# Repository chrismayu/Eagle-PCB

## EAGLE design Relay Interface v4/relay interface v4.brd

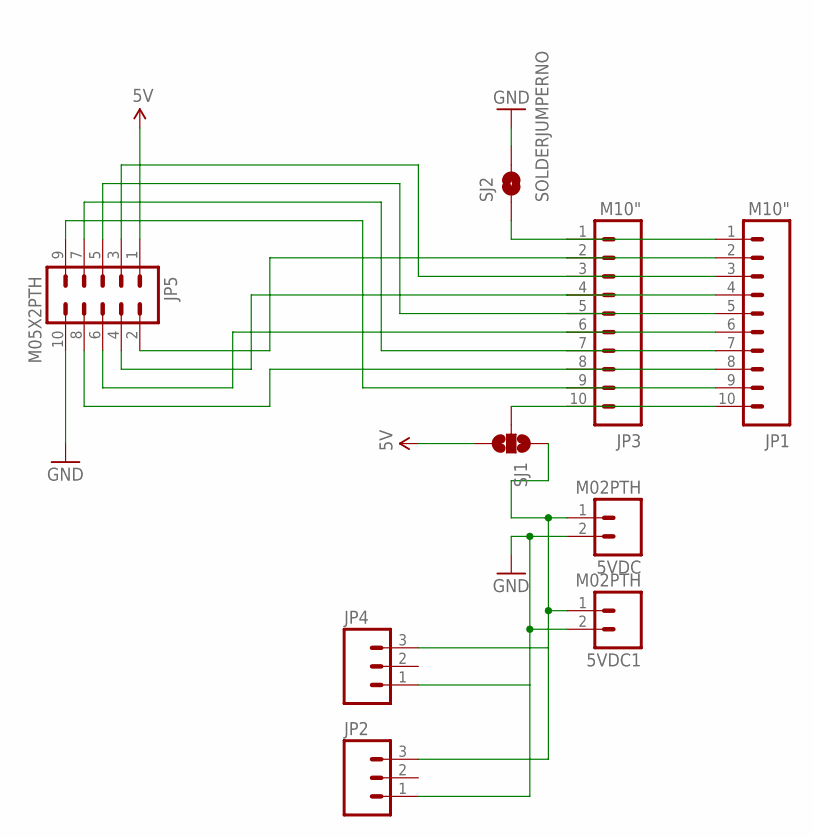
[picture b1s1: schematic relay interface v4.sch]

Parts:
5VDC, 5VDC1: M02PTH; 1X02
JP1, JP3: M10"; 1X10
JP2, JP4: M03PTH; 1X03
JP5: M05X2PTH; AVR_ICSP
SJ1: SOLDERJUMPER_2WAYS; SJ_3
SJ2: SOLDERJUMPERNO; SJ_2S-NO

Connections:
5V: JP5.1, SJ1.3
GND: 5VDC.2, 5VDC1.2, JP2.1, JP4.1, JP5.10, SJ2.2
unnamed: JP1.2, JP3.2, JP5.2
unnamed: JP1.3, JP3.3, JP5.3
unnamed: JP1.4, JP3.4, JP5.4
unnamed: JP1.5, JP3.5, JP5.5
unnamed: JP1.10, JP3.10, SJ1.2
unnamed: JP1.6, JP3.6, JP5.6
unnamed: JP1.7, JP3.7, JP5.7
unnamed: JP1.8, JP3.8, JP5.8
unnamed: JP1.9, JP3.9, JP5.9
unnamed: 5VDC.1, 5VDC1.1, JP2.3, JP4.3, SJ1.1
unnamed: JP1.1, JP3.1, SJ2.1

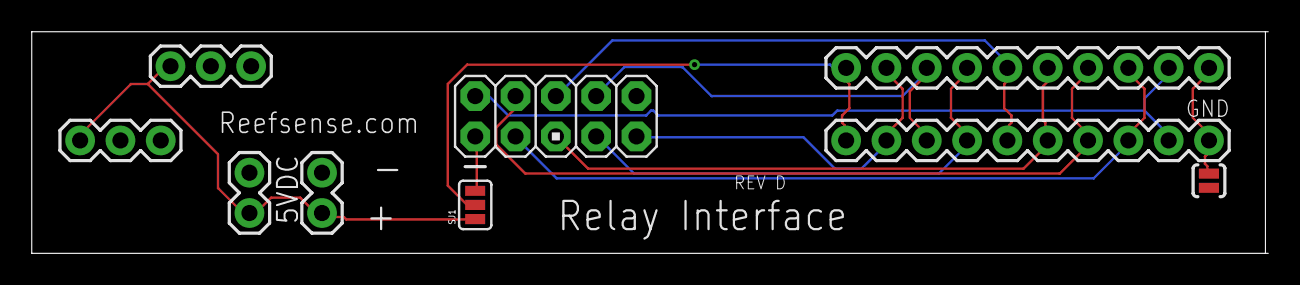
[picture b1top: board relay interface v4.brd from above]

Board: 2 copper layers, 77.7 x 14.0 mm, 9 parts (0 on the bottom side), 13 nets.

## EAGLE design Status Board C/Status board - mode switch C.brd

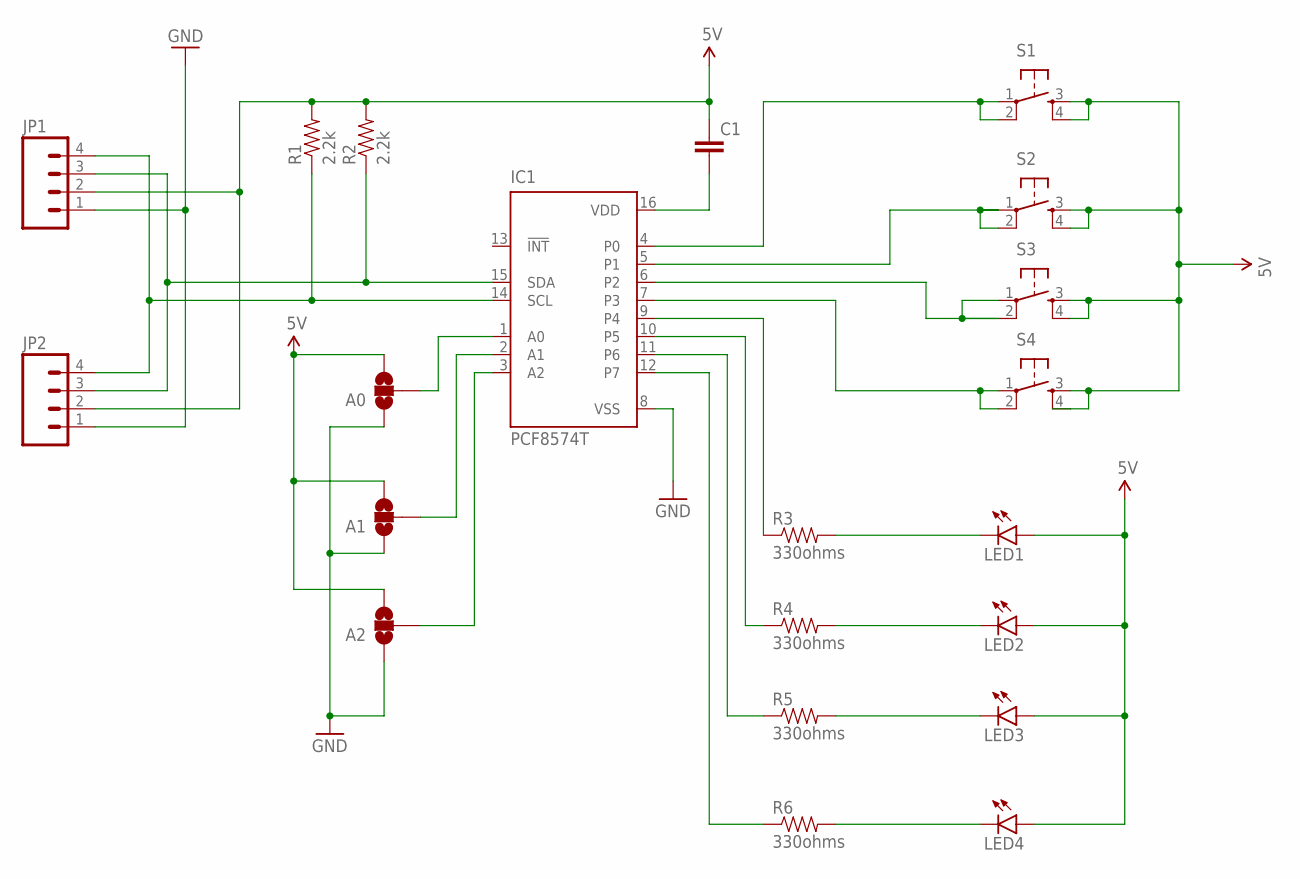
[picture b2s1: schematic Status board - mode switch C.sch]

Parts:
A0, A1, A2: SOLDERJUMPER_2WAYS; SJ_3
C1: CAPPTH2; CAP-PTH-SMALL2
IC1: PCF8574T; SO16W
JP1, JP2: M04PTH; 1X04
LED1, LED2, LED3, LED4: LED3MM
R1, R2: 2.2k; AXIAL-0.3
R3, R4, R5, R6: 330ohms; AXIAL-0.3
S1, S2, S3, S4: TAC_SWITCHPTH; TACTILE-PTH

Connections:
5V: A0.3, A1.3, A2.3, C1.1, JP1.2, JP2.2, LED1.A, LED2.A, LED3.A, LED4.A, R1.P$2 (2), R2.P$2 (2), S1.3, S1.4, S2.3, S2.4, S3.3, S3.4, S4.3, S4.4
GND: A0.1, A1.1, A2.1, IC1.8 (VSS), JP1.1, JP2.1
unnamed: IC1.5 (P1), S2.1, S2.2
unnamed: IC1.7 (P3), S4.1, S4.2
unnamed: IC1.6 (P2), S3.1, S3.2
unnamed: A1.2, IC1.2 (A1)
unnamed: IC1.14 (SCL), JP1.4, JP2.4, R1.P$1 (1)
unnamed: IC1.15 (SDA), JP1.3, JP2.3, R2.P$1 (1)
unnamed: A0.2, IC1.1 (A0)
unnamed: C1.2, IC1.16 (VDD)
unnamed: A2.2, IC1.3 (A2)
unnamed: LED4.K (C), R6.P$2 (2)
unnamed: IC1.9 (P4), R3.P$1 (1)
unnamed: IC1.10 (P5), R4.P$1 (1)
unnamed: IC1.11 (P6), R5.P$1 (1)
unnamed: IC1.12 (P7), R6.P$1 (1)
unnamed: LED3.K (C), R5.P$2 (2)
unnamed: LED2.K (C), R4.P$2 (2)
unnamed: LED1.K (C), R3.P$2 (2)
unnamed: IC1.4 (P0), S1.1, S1.2

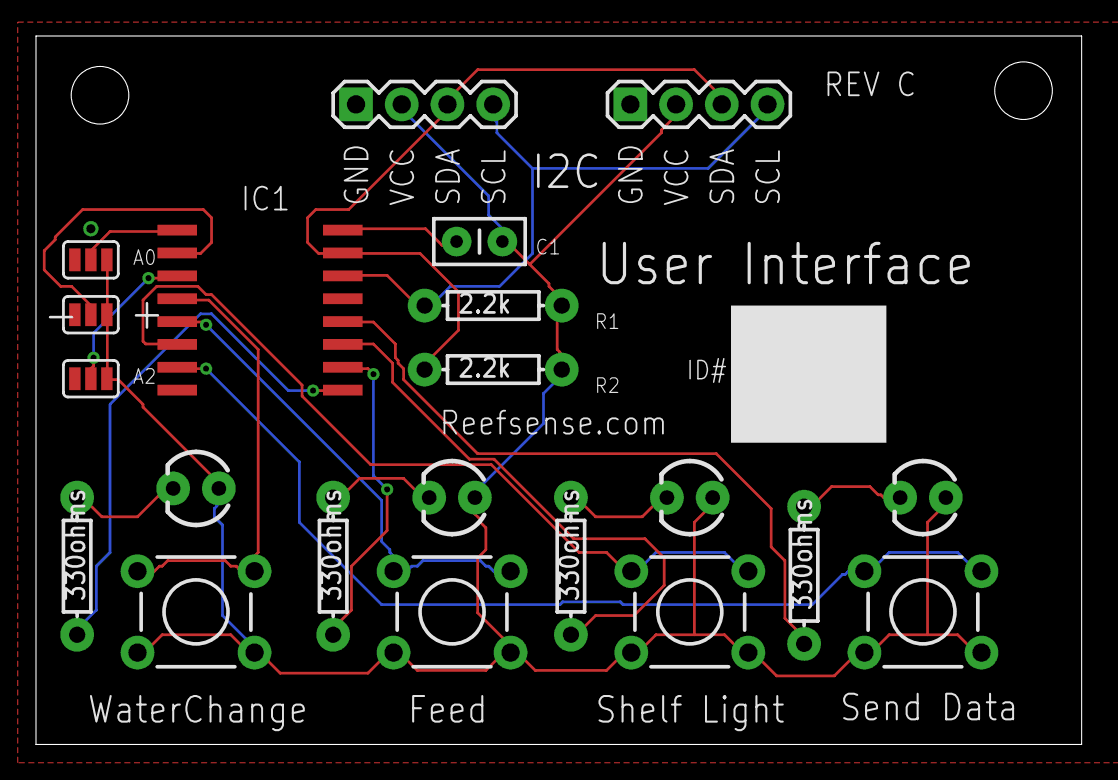
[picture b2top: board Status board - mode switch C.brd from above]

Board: 2 copper layers, 58.1 x 39.4 mm, 21 parts (0 on the bottom side), 20 nets.

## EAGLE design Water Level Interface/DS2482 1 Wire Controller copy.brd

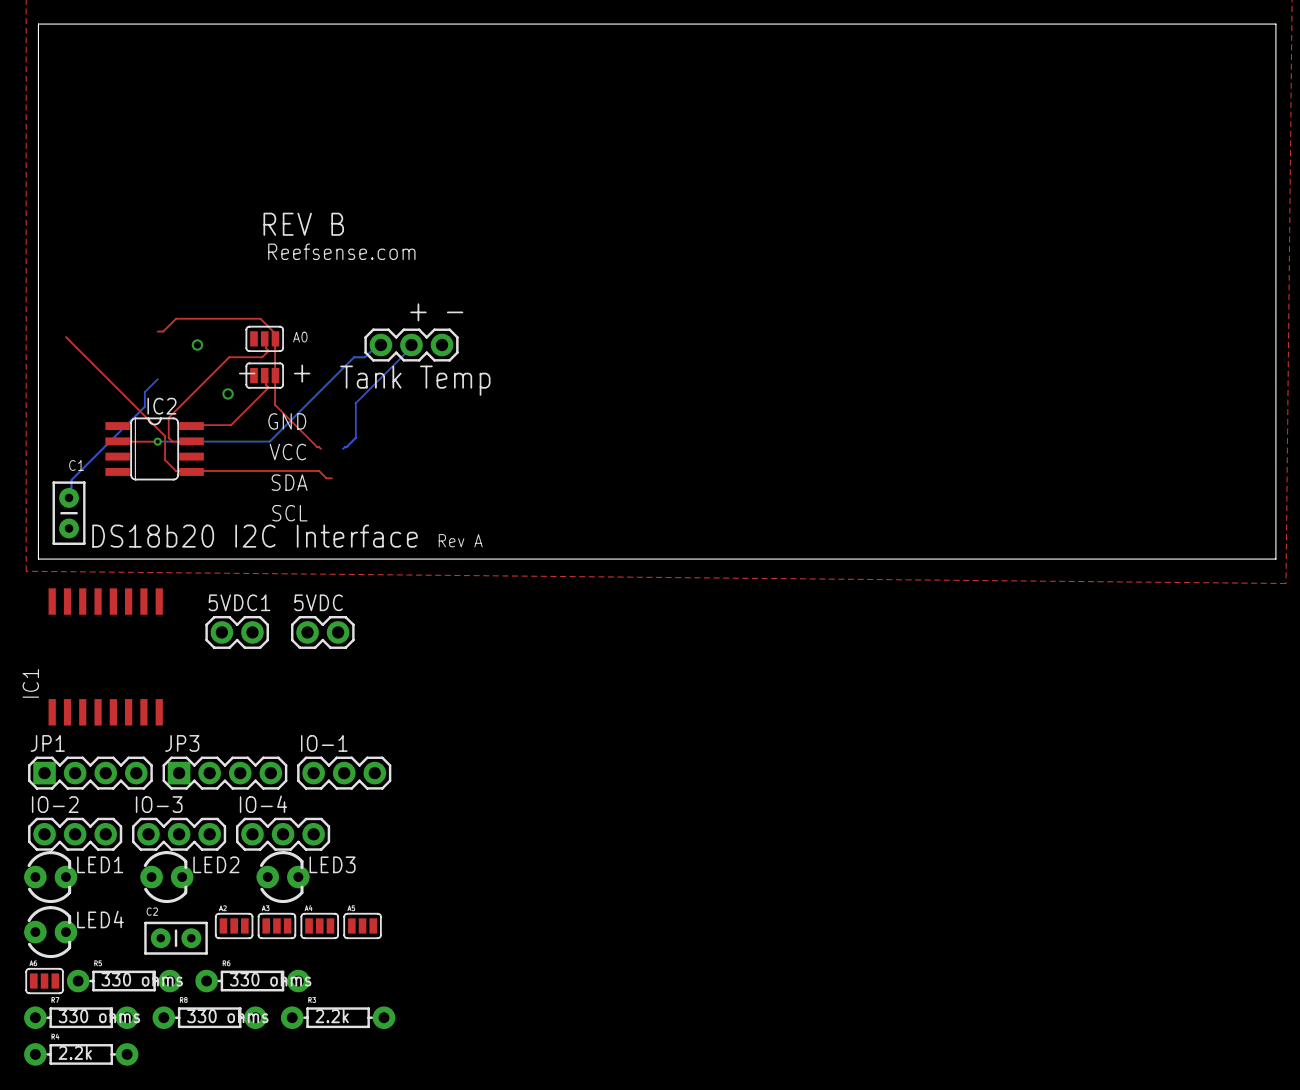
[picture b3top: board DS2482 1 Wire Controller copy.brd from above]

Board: 2 copper layers, 102.8 x 44.4 mm, 30 parts (0 on the bottom side), 27 nets.

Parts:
5VDC, 5VDC1: +; 1X02
A0, A1, A2, A3, A4, A5, A6: SJ_3
C1, C2: CAP-PTH-SMALL2
IC1: PCF8574T; SO16W
IC2: DS2482-100S; SO08
IO-1, IO-2, IO-3, IO-4: 1X03
JP1, JP3: 1X04
JP4: 1X03
LED1, LED2, LED3, LED4: LED3MM
R3, R4: 2.2k; AXIAL-0.3
R5, R6, R7, R8: 330 ohms; AXIAL-0.3

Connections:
5V: A0.3, A1.3, A2.3, A3.3, A4.3, A6.1, C1.1, C2.1, JP1.2, JP3.2, JP4.2, LED1.A, LED2.A, LED3.A, LED4.A, R3.P$2, R4.P$2
GND: A0.1, A1.1, A2.1, A3.1, A4.1, A5.3, C1.2, IC1.8, IC2.3, JP1.1, JP3.1, JP4.3
unnamed: IC1.14, IC2.4, JP1.4, JP3.4, R4.P$1
unnamed: A2.2, IC1.1
unnamed: A0.2, IC2.7
unnamed: IC1.15, IC2.5, JP1.3, JP3.3, R3.P$1
unnamed: A1.2, IC2.8
unnamed: C2.2, IC1.16
unnamed: A3.2, IC1.2
unnamed: A4.2, IC1.3
unnamed: IC1.10, R6.P$1
unnamed: IC2.2, JP4.1
unnamed: IC1.11, R7.P$1
unnamed: IC1.12, R8.P$1
unnamed: IC1.4, IO-1.1
unnamed: IC1.5, IO-2.1
unnamed: IC1.6, IO-3.1
unnamed: IC1.7, IO-4.1
unnamed: IC1.9, R5.P$1
unnamed: LED1.K, R5.P$2
unnamed: LED2.K, R6.P$2
unnamed: LED3.K, R7.P$2
unnamed: LED4.K, R8.P$2
unnamed: A6.2, IO-1.2, IO-2.2, IO-3.2, IO-4.2
unnamed: 5VDC.1, 5VDC1.1, A6.3
unnamed: 5VDC.2, 5VDC1.2, A5.1
unnamed: A5.2, IO-1.3, IO-2.3, IO-3.3, IO-4.3

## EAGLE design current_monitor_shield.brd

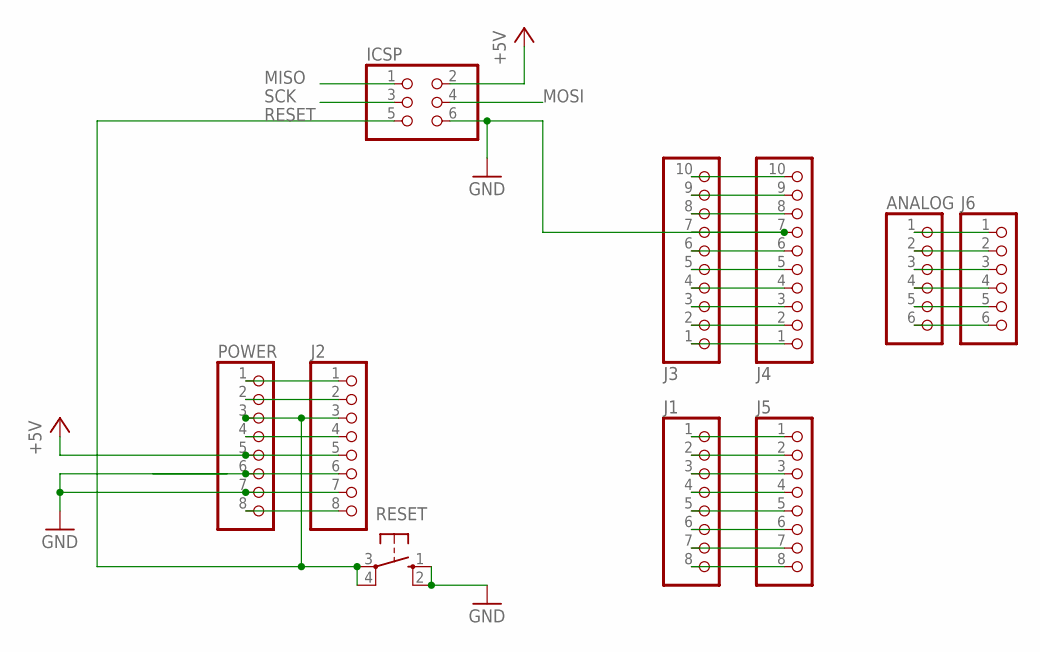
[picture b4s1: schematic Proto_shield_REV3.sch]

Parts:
ANALOG: PINHD-1X6; 1X06
ICSP: PINHD-2X3; 2X03
J1, J2, J5: PINHD-1X8TH; 1X08-TH
J3, J4: PINHD-1X10TH; 1X10-TH
J6: PINHD-1X6; 1X06
POWER: PINHD-1X8TH; 1X08-TH
RESET: 10-XX; B3F-10XX

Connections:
+5V: ICSP.2, J2.5, POWER.5
+9V: J2.8, POWER.8
GND: ICSP.6, J2.7, J3.7, J4.7, POWER.7, RESET.1 (S), RESET.2 (S1)
MISO: ICSP.1
MOSI: ICSP.4
unnamed: J3.6, J4.6
unnamed: J3.1, J4.1
unnamed: J3.4, J4.4
unnamed: J3.5, J4.5
unnamed: J3.2, J4.2
unnamed: J3.3, J4.3
unnamed: J1.1, J5.1
unnamed: J1.2, J5.2
unnamed: J1.3, J5.3
unnamed: J1.4, J5.4
unnamed: J1.5, J5.5
unnamed: J1.6, J5.6
unnamed: J1.7, J5.7
unnamed: J1.8, J5.8
unnamed: ANALOG.1, J6.1
unnamed: ANALOG.2, J6.2
unnamed: ANALOG.3, J6.3
unnamed: ANALOG.4, J6.4
unnamed: ANALOG.5, J6.5
unnamed: ANALOG.6, J6.6
unnamed: J2.6, POWER.6
unnamed: J2.2, POWER.2
unnamed: J2.1, POWER.1
unnamed: J3.9, J4.9
unnamed: J3.10, J4.10
unnamed: J3.8, J4.8
unnamed: J2.4, POWER.4
RESET: ICSP.5, J2.3, POWER.3, RESET.3, RESET.4 (P1)
SCK: ICSP.3

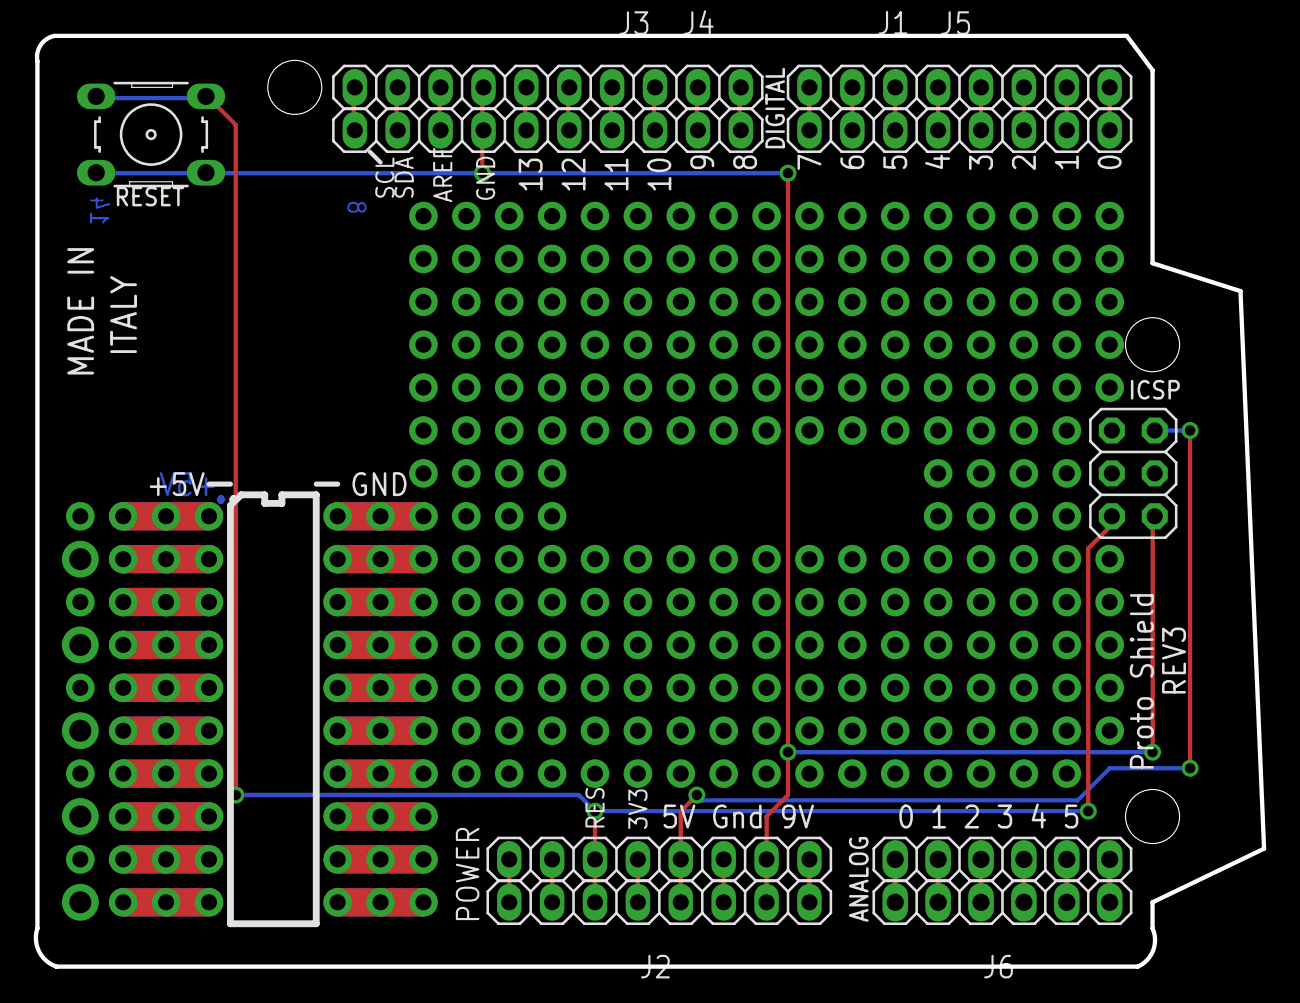
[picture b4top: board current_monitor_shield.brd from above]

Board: 2 copper layers, 72.7 x 55.1 mm, 10 parts (0 on the bottom side), 31 nets.

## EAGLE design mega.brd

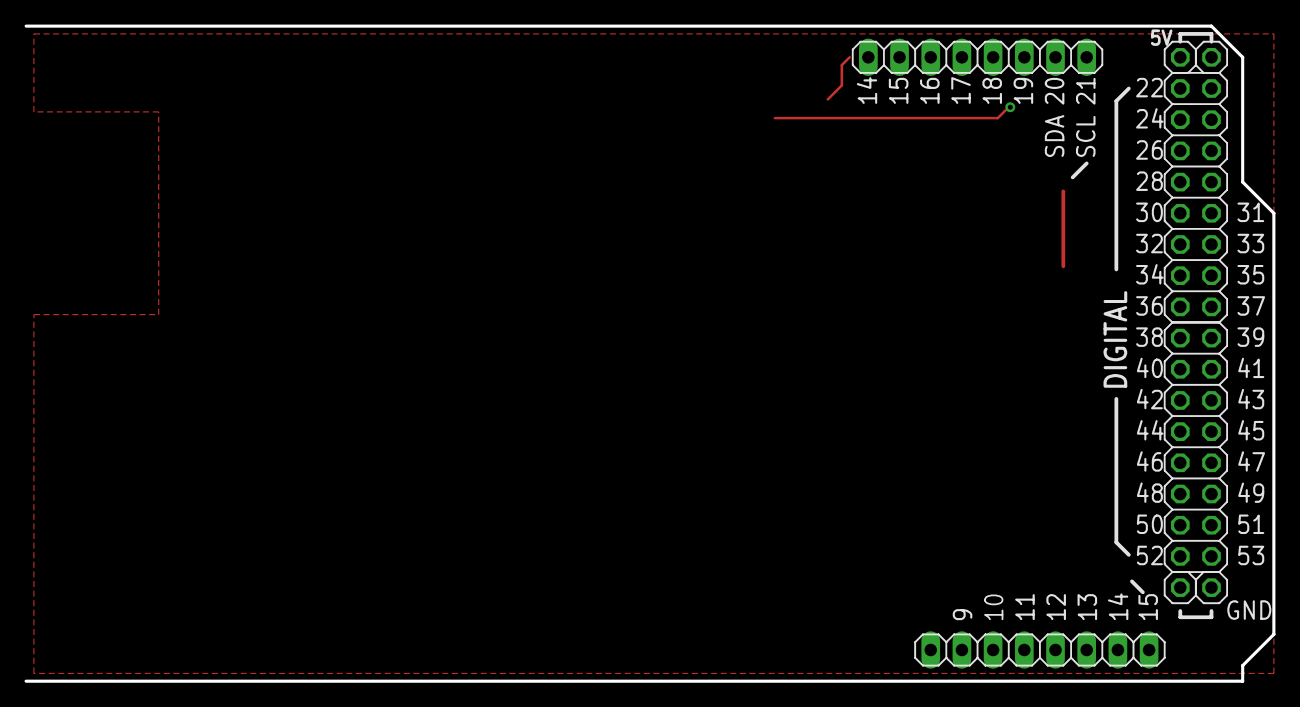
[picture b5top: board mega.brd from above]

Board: 2 copper layers, 101.6 x 53.3 mm, 8 parts (0 on the bottom side), 2 nets.

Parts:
ADCH: 1X08
COMMUNICATION: 1X08
JP1, JP2, JP3, JP4: 1X01
XIOH: 2X08
XIOL: 2X08

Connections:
+5V: JP1.1, JP2.1
GND: JP3.1, JP4.1

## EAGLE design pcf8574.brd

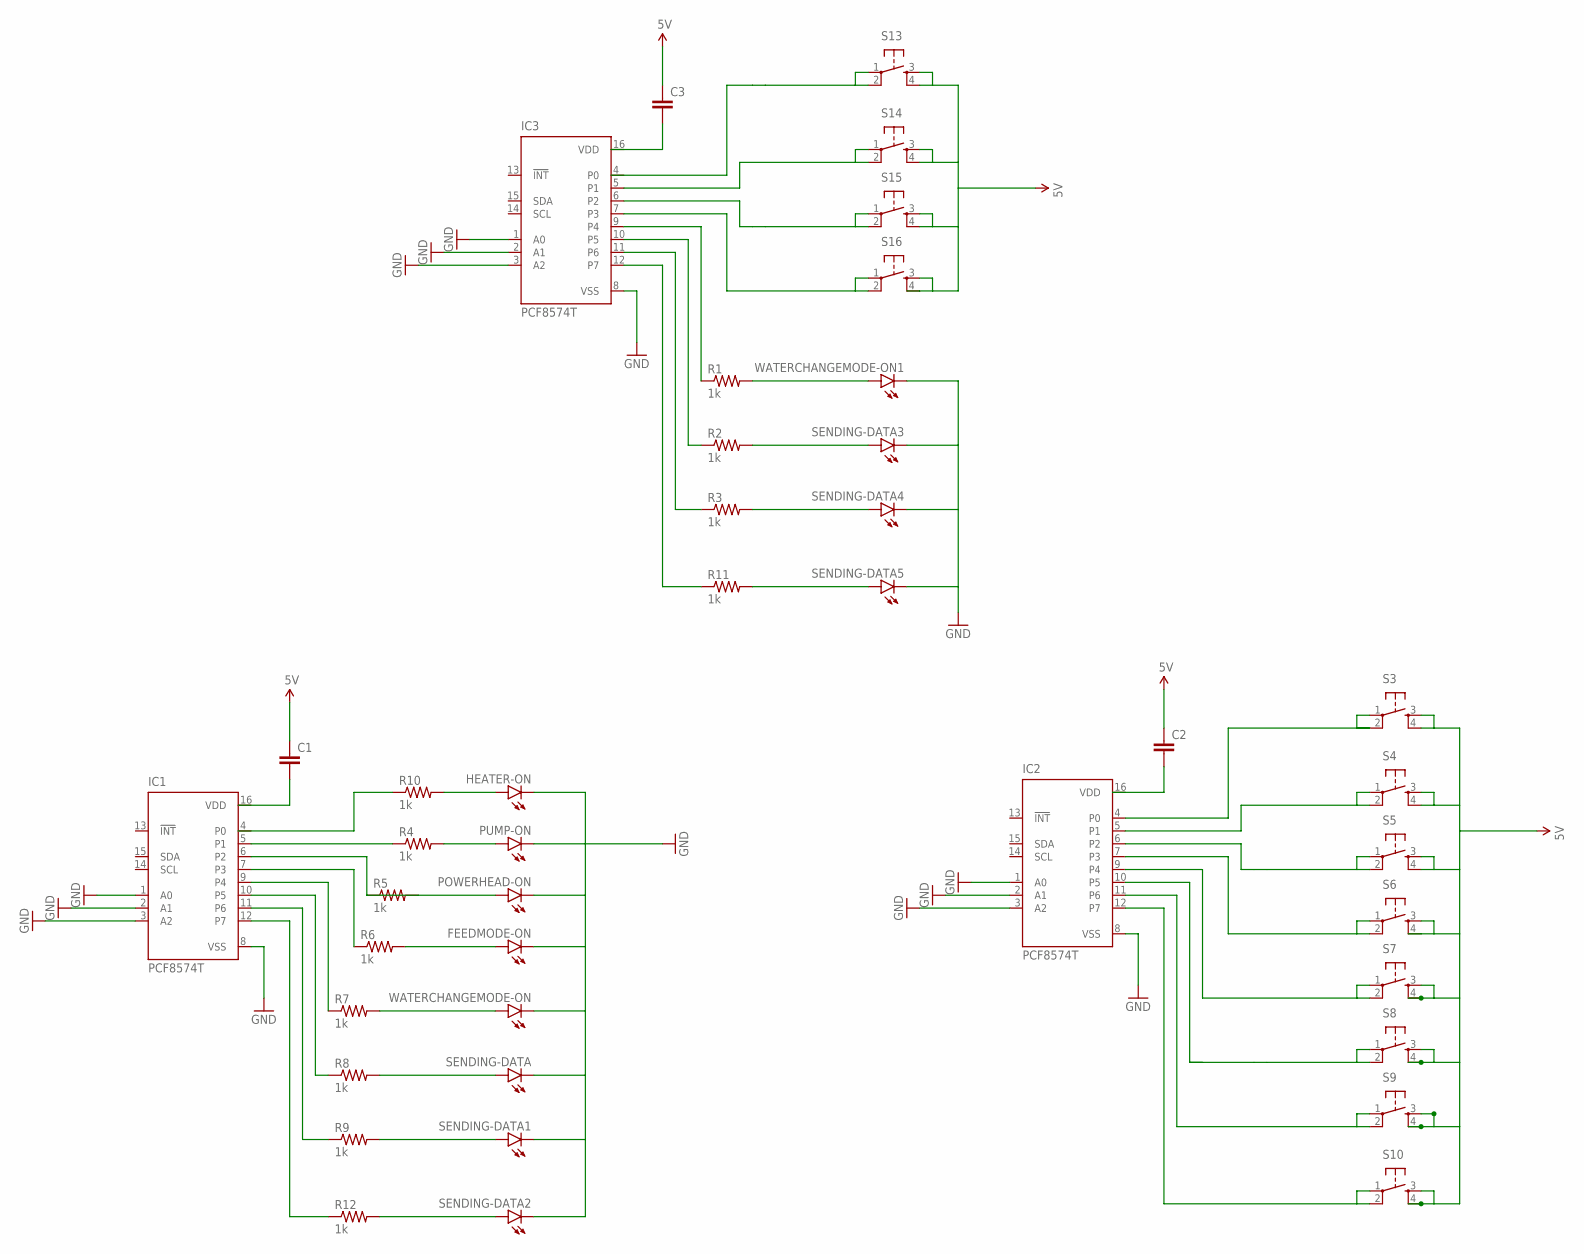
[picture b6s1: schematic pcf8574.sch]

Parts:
C1, C2, C3: CAPPTH2; CAP-PTH-SMALL2
FEEDMODE-ON: LED3MM
HEATER-ON: LED3MM
IC1, IC2, IC3: PCF8574T; SO16W
POWERHEAD-ON: LED3MM
PUMP-ON: LED3MM
R1, R2, R3, R4, R5, R6, R7, R8, R9, R10, R11, R12: 1k; AXIAL-0.3
S3, S4, S5, S6, S7, S8, S9, S10, S13, S14, S15, S16: TAC_SWITCHPTH; TACTILE-PTH
SENDING-DATA, SENDING-DATA1, SENDING-DATA2, SENDING-DATA3, SENDING-DATA4, SENDING-DATA5: LED3MM
WATERCHANGEMODE-ON, WATERCHANGEMODE-ON1: LED3MM

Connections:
5V: C1.1, C2.1, C3.1, S3.3, S3.4, S4.3, S4.4, S5.3, S5.4, S6.3, S6.4, S7.3, S7.4, S8.3, S8.4, S9.3, S9.4, S10.3, S10.4, S13.3, S13.4, S14.3, S14.4, S15.3, S15.4, S16.3, S16.4
GND: FEEDMODE-ON.K (C), HEATER-ON.K (C), IC1.1 (A0), IC1.2 (A1), IC1.3 (A2), IC1.8 (VSS), IC2.1 (A0), IC2.2 (A1), IC2.3 (A2), IC2.8 (VSS), IC3.1 (A0), IC3.2 (A1), IC3.3 (A2), IC3.8 (VSS), POWERHEAD-ON.K (C), PUMP-ON.K (C), SENDING-DATA.K (C), SENDING-DATA1.K (C), SENDING-DATA2.K (C), SENDING-DATA3.K (C), SENDING-DATA4.K (C), SENDING-DATA5.K (C), WATERCHANGEMODE-ON.K (C), WATERCHANGEMODE-ON1.K (C)
unnamed: PUMP-ON.A, R4.P$2 (2)
unnamed: HEATER-ON.A, R10.P$2 (2)
unnamed: R9.P$2 (2), SENDING-DATA1.A
unnamed: R12.P$2 (2), SENDING-DATA2.A
unnamed: R8.P$2 (2), SENDING-DATA.A
unnamed: R7.P$2 (2), WATERCHANGEMODE-ON.A
unnamed: IC1.12 (P7), R12.P$1 (1)
unnamed: IC1.11 (P6), R9.P$1 (1)
unnamed: IC1.10 (P5), R8.P$1 (1)
unnamed: IC1.9 (P4), R7.P$1 (1)
unnamed: IC1.7 (P3), R6.P$1 (1)
unnamed: FEEDMODE-ON.A, R6.P$2 (2)
unnamed: IC1.6 (P2), POWERHEAD-ON.A, R5.P$1 (1), R5.P$2 (2)
unnamed: IC1.5 (P1), R4.P$1 (1)
unnamed: IC2.11 (P6), S9.1, S9.2
unnamed: IC2.12 (P7), S10.1, S10.2
unnamed: S8.1, S8.2
unnamed: IC2.9 (P4), S7.1, S7.2
unnamed: IC3.11 (P6), R3.P$1 (1)
unnamed: IC3.12 (P7), R11.P$1 (1)
unnamed: IC3.9 (P4), R1.P$1 (1)
unnamed: IC2.7 (P3), S6.1, S6.2
unnamed: IC3.10 (P5), R2.P$1 (1)
unnamed: IC2.5 (P1), S4.1, S4.2
unnamed: IC2.4 (P0), S3.1, S3.2
unnamed: IC3.7 (P3), S16.1, S16.2
unnamed: IC3.5 (P1), S14.1, S14.2
unnamed: IC2.6 (P2), S5.1, S5.2
unnamed: S13.1, S13.2
unnamed: IC3.6 (P2), S15.1, S15.2
unnamed: R3.P$2 (2), SENDING-DATA4.A
unnamed: R11.P$2 (2), SENDING-DATA5.A
unnamed: R2.P$2 (2), SENDING-DATA3.A
unnamed: R1.P$2 (2), WATERCHANGEMODE-ON1.A
VDD: IC1.16 (VDD), IC2.16 (VDD), IC3.16 (VDD)

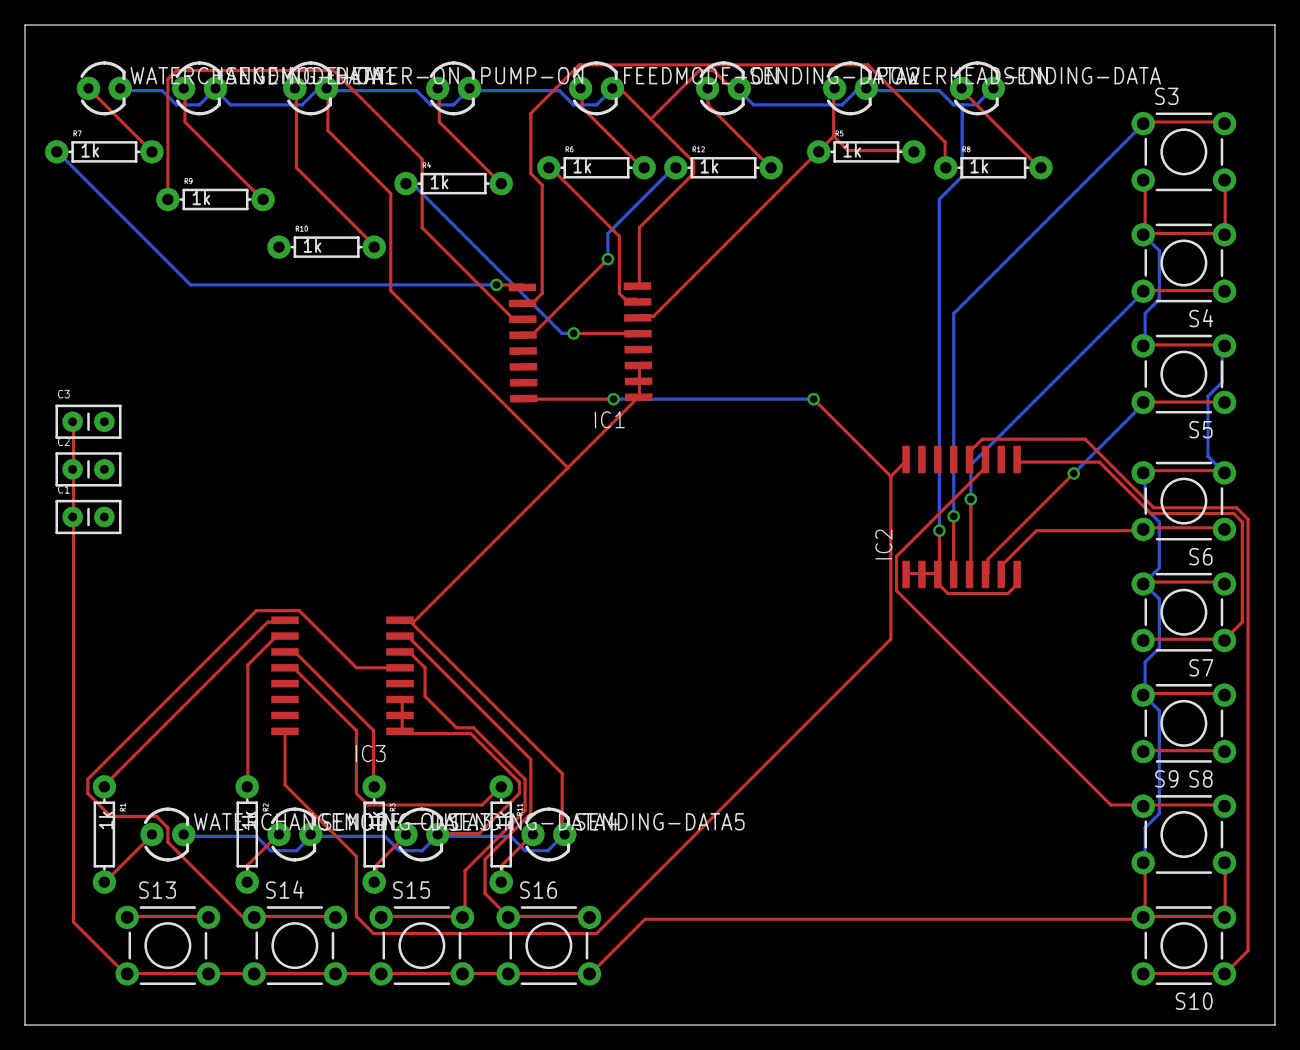
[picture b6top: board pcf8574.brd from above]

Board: 2 copper layers, 100.0 x 80.0 mm, 42 parts (0 on the bottom side), 37 nets.

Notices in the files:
parts and their libraries:
SparkFun-Connectors: Licensing: Creative Commons ShareAlike 4.0 International - https://creativecommons.org/licenses/by-sa/4.0
